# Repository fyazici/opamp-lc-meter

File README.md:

# opamp-lc-meter
Simple LC oscillator PCB design built with LM393

A replica of the oscillator section of Kerry Wong's LC meter design (http://www.kerrywong.com/2010/10/16/avr-lc-meter-with-frequency-measurement)

3D view of the board:

Note that the frequency counter section is not included in this board. This board is useful only if one has an actual (preferably more accurate than an MCU) frequency counter.

Connector usage (power, output etc.) can be deduced from the schematic.

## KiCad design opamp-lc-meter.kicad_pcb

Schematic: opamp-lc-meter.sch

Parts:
C1: 1n; C_Rect_L7.0mm_W2.0mm_P5.00mm
C2: 10u; CP_Radial_D5.0mm_P2.50mm
C3: 10U; CP_Radial_D5.0mm_P2.50mm
J1: Conn_01x04; PinHeader_1x04_P2.54mm_Vertical
J2, J3: Conn_02x04_Counter_Clockwise; DIP-8_W7.62mm_Socket_LongPads
J4, J5: Conn_01x02; PinHeader_1x02_P2.54mm_Vertical
L1: 220U; L_Axial_L7.0mm_D3.3mm_P12.70mm_Horizontal_Fastron_MICC
R1, R2, R3, R4: 47K; R_Axial_DIN0207_L6.3mm_D2.5mm_P10.16mm_Horizontal
R5: 1K; R_Axial_DIN0207_L6.3mm_D2.5mm_P10.16mm_Horizontal
R6, R7, R8: 15K; R_Axial_DIN0207_L6.3mm_D2.5mm_P10.16mm_Horizontal
U1: LM393; DIP-8_W7.62mm_LongPads

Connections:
GND: C1.2, C3.2, J1.3, J1.4, J2.1, J2.2, J2.3, J2.4, J3.1, J3.2, J3.3, J3.4, J5.1, J5.2, R2.2, R7.2, U1.4 (V-)
unnamed: C1.1, C2.2, J3.5, J3.6, J3.7, J3.8, L1.2
unnamed: C2.1, R1.2, R2.1, R3.2, U1.3 (+)
unnamed: C3.1, R4.2, U1.2 (_)
unnamed: J2.5, J2.6, J2.7, J2.8, L1.1
unnamed: J4.1, J4.2, R8.1, U1.7
unnamed: R3.1, R4.1, R5.2, U1.1, U1.6 (_)
unnamed: R6.2, R7.1, R8.2, U1.5 (+)
VCC: J1.1, J1.2, R1.1, R5.1, R6.1, U1.8 (V+)

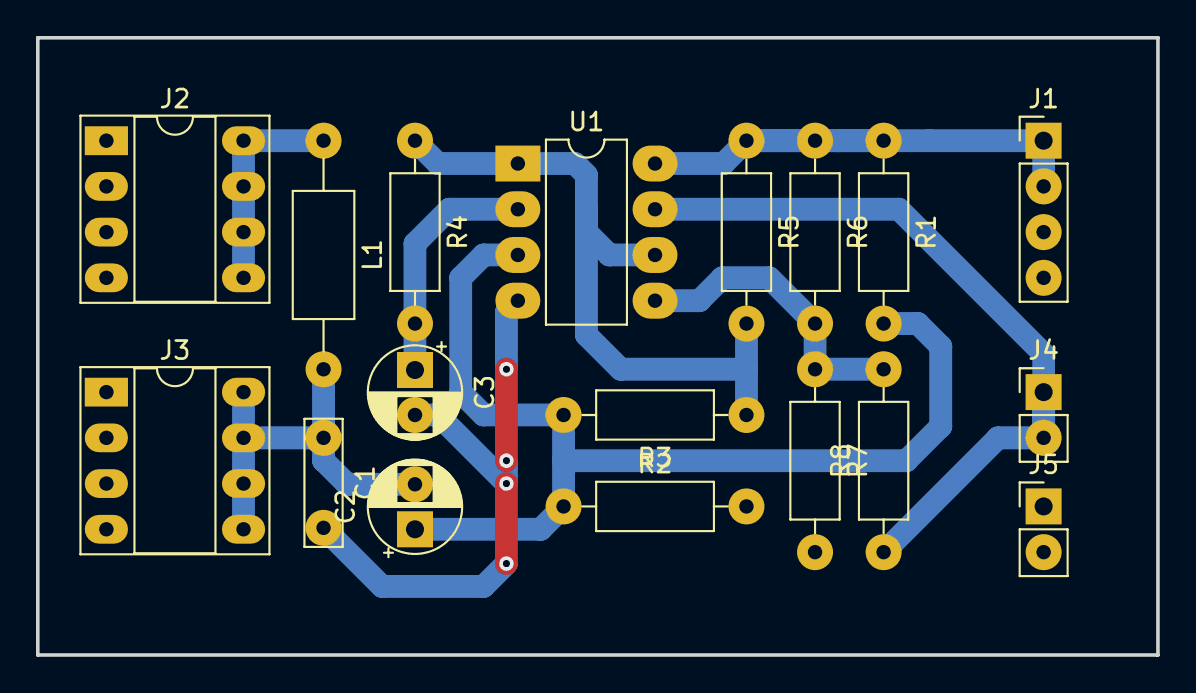
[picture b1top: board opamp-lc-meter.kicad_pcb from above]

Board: 2 copper layers, 62.2 x 34.3 mm, 18 parts (0 on the bottom side), 9 nets.

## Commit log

2018-02-14 Change footprint of component socket to an actual socket
2018-02-14 new footprint association file
2018-02-14 rendered board 3d view
